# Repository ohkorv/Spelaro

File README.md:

<h1 align="center">

<br> Spelarö <br>

<h4 align="center">
A standalone audio player and optical transmitter powered by the ESP32-S3. Play FLAC and MP3 files from a micro SD card, navigate your library using the 2.8-inch screen and 5-way switch, and output clean digital audio via TOSLINK.
</h4>

<h4 align="center">

<h4 align="center">

# About the project

Spelarö is a custom hardware project that lets you play flac and mp3 files directly from a micro SD card. It sends the data optically via a toslink transmitter with a toslink cable. There was no product like this, so i decided to make my own for me and my dad.

## How It Works

* **Storage:** Music files are stored on a standard micro SD card. The ESP32-S3 reads the files directly from the card. It then sends it via toslink.
* **Interface:** You use a 2.8-inch TFT display to see your library and a 5-way joystick switch to navigate through your libary of songs. 
* **Audio Output:** The ESP32-S3 processes the audio data and sends it out through a toslink transmitter. This results in perfect audio for audiophiles like me and my dad. 
* **Status LED:** An onboard NeoPixel (WS2812B) provides visual feedback for power status and can be programmed to follow the song's rhythm or anything you want.

## Features

* **ESP32-S3-NANO** microcontroller
* **1x 2.8" TFT Display** 
* **1x 5-way tactile joystick switch** 
* **1x 1-way tactile switch** 
* **1x Micro SD Card Reader** 
* **1x Neopixel WS2812B** 
* **1x Optical Toslink Transmitter (OTJ-5)** 

# Schematic

# PCB

# Bill Of Materials

| Designator | Footprint | Qty | Value | Link | Price (USD) |
| :--- | :--- | :---: | :--- | :--- | :---: |
| A1 | `MODULE_NANO-ESP32-ENTRY` | 1 | Arduino_Nano_ESP32 | [Electrokit](https://www.electrokit.com/utvecklingskort-esp32-s3-nano-kompatibelt) | $16.72 |
| C1 | `1206` | 1 | 100nF | [Electrokit](https://www.electrokit.com/kondensator-1206-x7r-100nf-10) | $1.05 |
| J1 | `PinHeader_1x14_P2.54mm_Vertical` | 1 | Conn_01x14_Pin | [Amazon](https://www.amazon.se/gp/product/B09Z29CGY1/ref=ox_sc_act_image_1?smid=A3LA1TDA4Q3SUA&psc=1) | $13.67 |
| LED1 | `WS2812B` | 1 | WS2812B | [Electrokit](https://www.electrokit.com/led-smd5050-rgb-adresserbar-sk6812) | $1.31 |
| R1, R2, R3 | `1206` | 3 | 10k | [Electrokit](https://www.electrokit.com/motstand-10kohm-0.25w-smd-1206) | $1.05 |
| S1 | `SW_VS-1213-67-160GF` | 1 | VS-1213-67-160GF | [Electrokit](https://www.electrokit.com/tryckknapp-pcb-12x12x5mm) | $1.35 |
| SW1 | `C145910` | 1 | K1-1506SN-01 | [Electrokit](https://www.electrokit.com/joystick-navigationsknapp-5-vags-smd-10x10mm-1) | $1.95 |
| TF1 | `TF-SMD_TF-012` | 1 | TF-CARD H1.8 SY | [Electrokit](https://www.electrokit.com/kontakt-microsd) | $1.37 |
| U3 | `toslink` | 1 | OTJ-5 | [Electrokit](https://www.electrokit.com/toslink-optisk-sandare-pcb) | $2.94 |
| PCB | - | 5 | - | [JLCPCB](https://jlcpcb.com/) | $2.10 |
| **Shipping** | - | - | - | - | $33.01 |
| **Total** | - | - | - | - | **$76.52** |

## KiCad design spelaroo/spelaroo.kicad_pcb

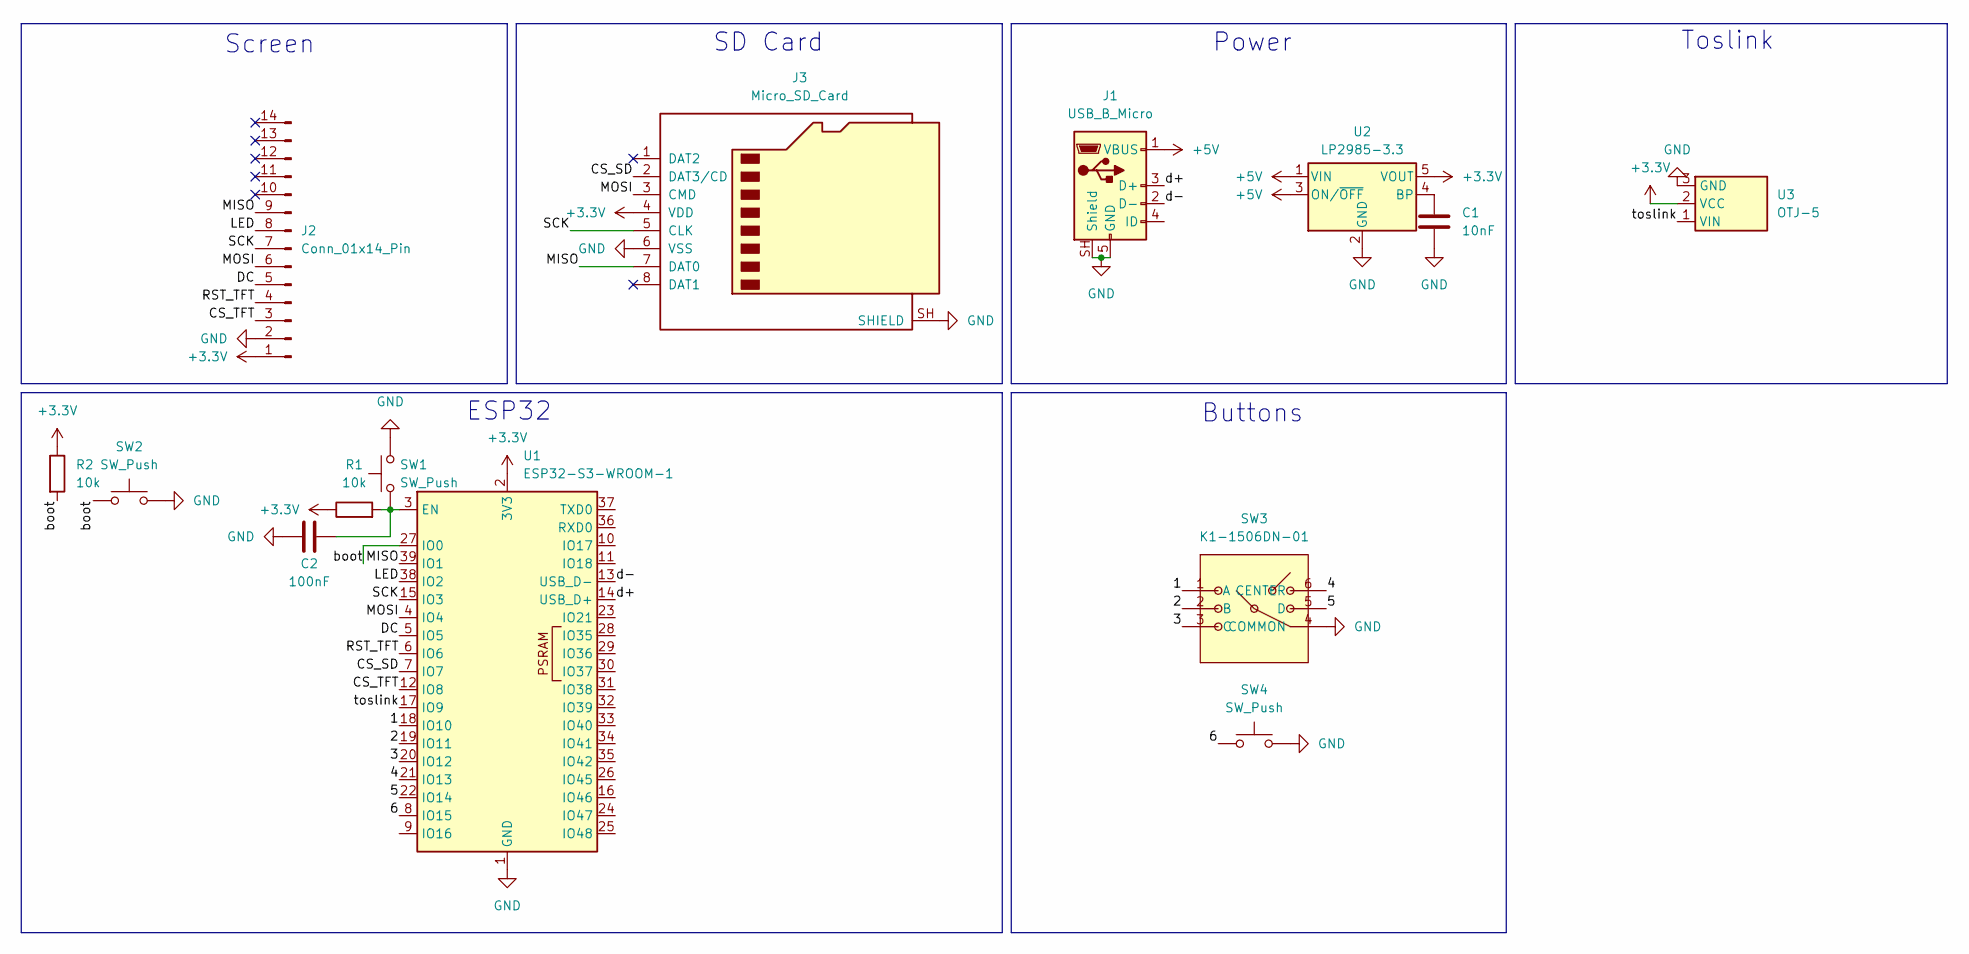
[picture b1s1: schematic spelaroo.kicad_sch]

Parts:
C1: 10nF; C_1206_3216Metric
C2: 100nF; C_1206_3216Metric
J1: USB_B_Micro; USB_Micro-B_Amphenol_10103594-0001LF_Horizontal
J2: Conn_01x14_Pin; PinHeader_1x14_P2.54mm_Vertical
J3: Micro_SD_Card; TF-SMD_TF-012
R1, R2: 10k; R_1206_3216Metric
SW1, SW2: SW_Push; KSR221GLFS_CNK
SW3: K1-1506DN-01; SW-TH_K1-1506DN-01; MPN K1-1506DN-01; LCSC Part C145911
SW4: SW_Push; SW_PUSH-12mm
U1: ESP32-S3-WROOM-1
U2: LP2985-3.3; SOT-23-5
U3: OTJ-5; toslink

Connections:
+3.3V: J2.1, J3.4 (VDD), R1.1, R2.1, U1.2 (3V3), U2.5 (VOUT), U3.2 (VCC)
+5V: J1.1 (VBUS), U2.1 (VIN), U2.3 (ON/~OFF)
/1: SW3.1 (A), U1.18 (IO10)
/2: SW3.2 (B), U1.19 (IO11)
/3: SW3.3 (C), U1.20 (IO12)
/4: SW3.6 (CENTER), U1.21 (IO13)
/5: SW3.5 (D), U1.22 (IO14)
/6: SW4.1, U1.8 (IO15)
/CS_SD: J3.2 (DAT3/CD), U1.7 (IO7)
/CS_TFT: J2.3, U1.12 (IO8)
/DC: J2.5, U1.5 (IO5)
/LED: J2.8, U1.38 (IO2)
/MISO: J2.9, J3.7 (DAT0), U1.39 (IO1)
/MOSI: J2.6, J3.3 (CMD), U1.4 (IO4)
/RST_TFT: J2.4, U1.6 (IO6)
/SCK: J2.7, J3.5 (CLK), U1.15 (IO3)
/boot: R2.2, SW2.1, U1.27 (IO0)
/d+: J1.3 (D+), U1.14 (USB_D+)
/d-: J1.2 (D-), U1.13 (USB_D-)
/toslink: U1.17 (IO9), U3.1 (VIN)
GND: C1.2, C2.2, J1.5 (GND), J1.SH (Shield), J2.2, J3.6 (VSS), J3.SH (SHIELD), SW1.2, SW2.2, SW3.4 (COMMON), SW4.2, U1.1 (GND), U1.40 (GND), U1.41 (GND), U2.2 (GND), U3.3 (GND)
unnamed: C2.1, R1.2, SW1.1, U1.3 (EN)
unnamed: C1.1, U2.4 (BP)

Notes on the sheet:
Screen
Toslink
ESP32
Buttons
SD Card
Power

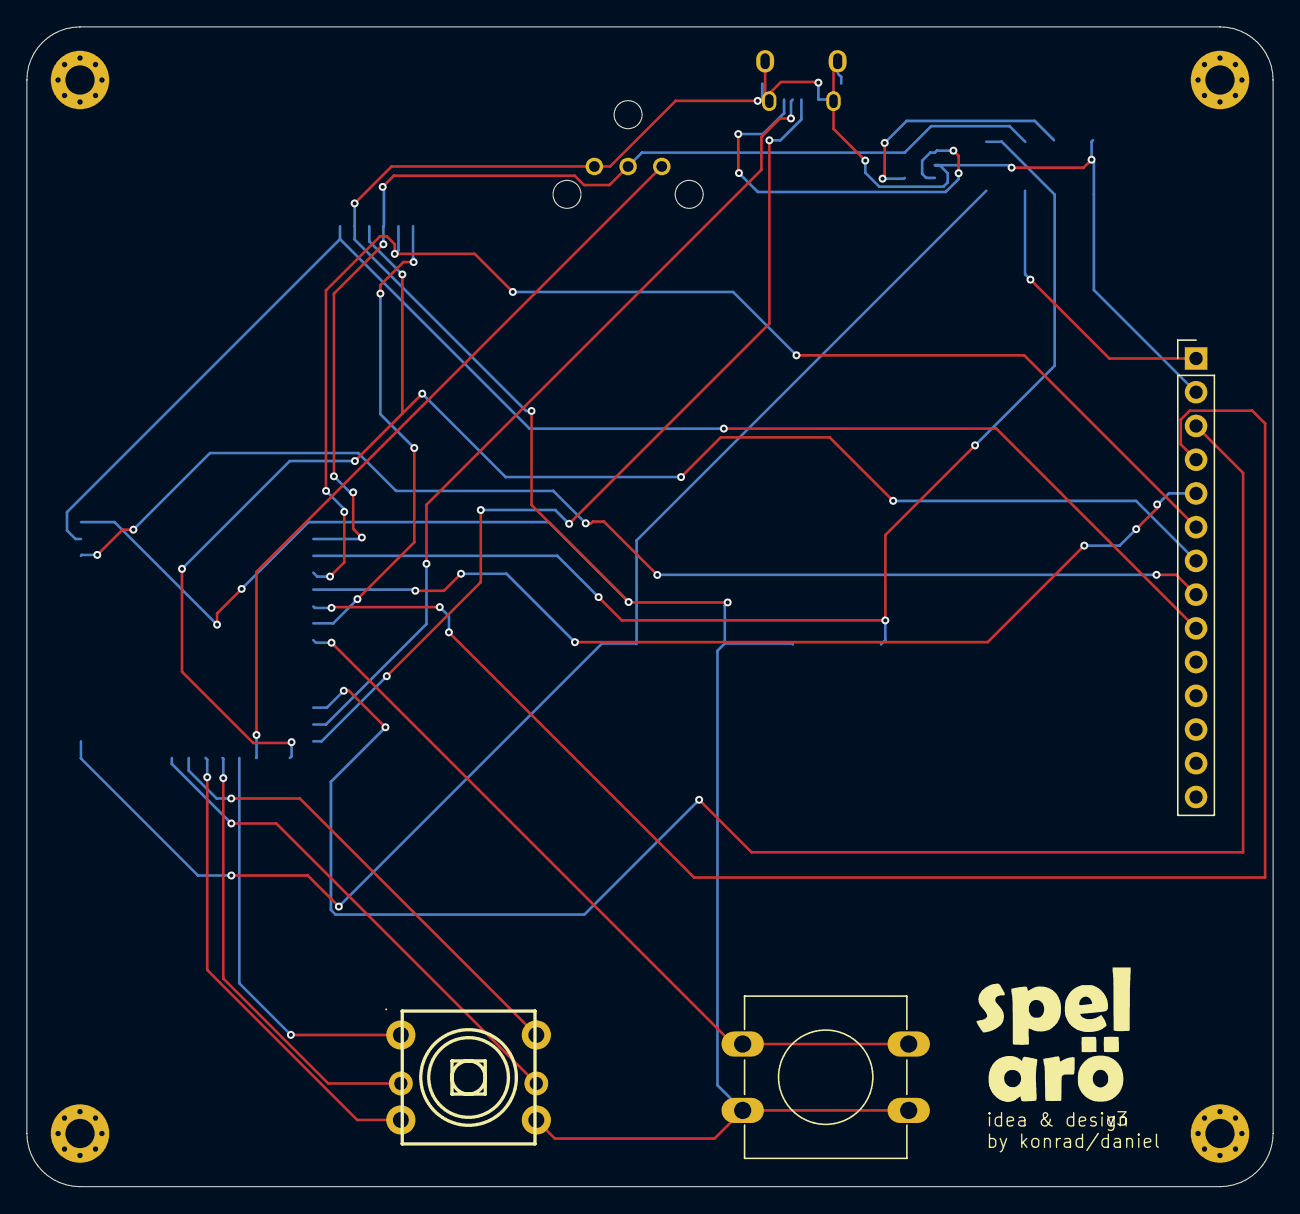
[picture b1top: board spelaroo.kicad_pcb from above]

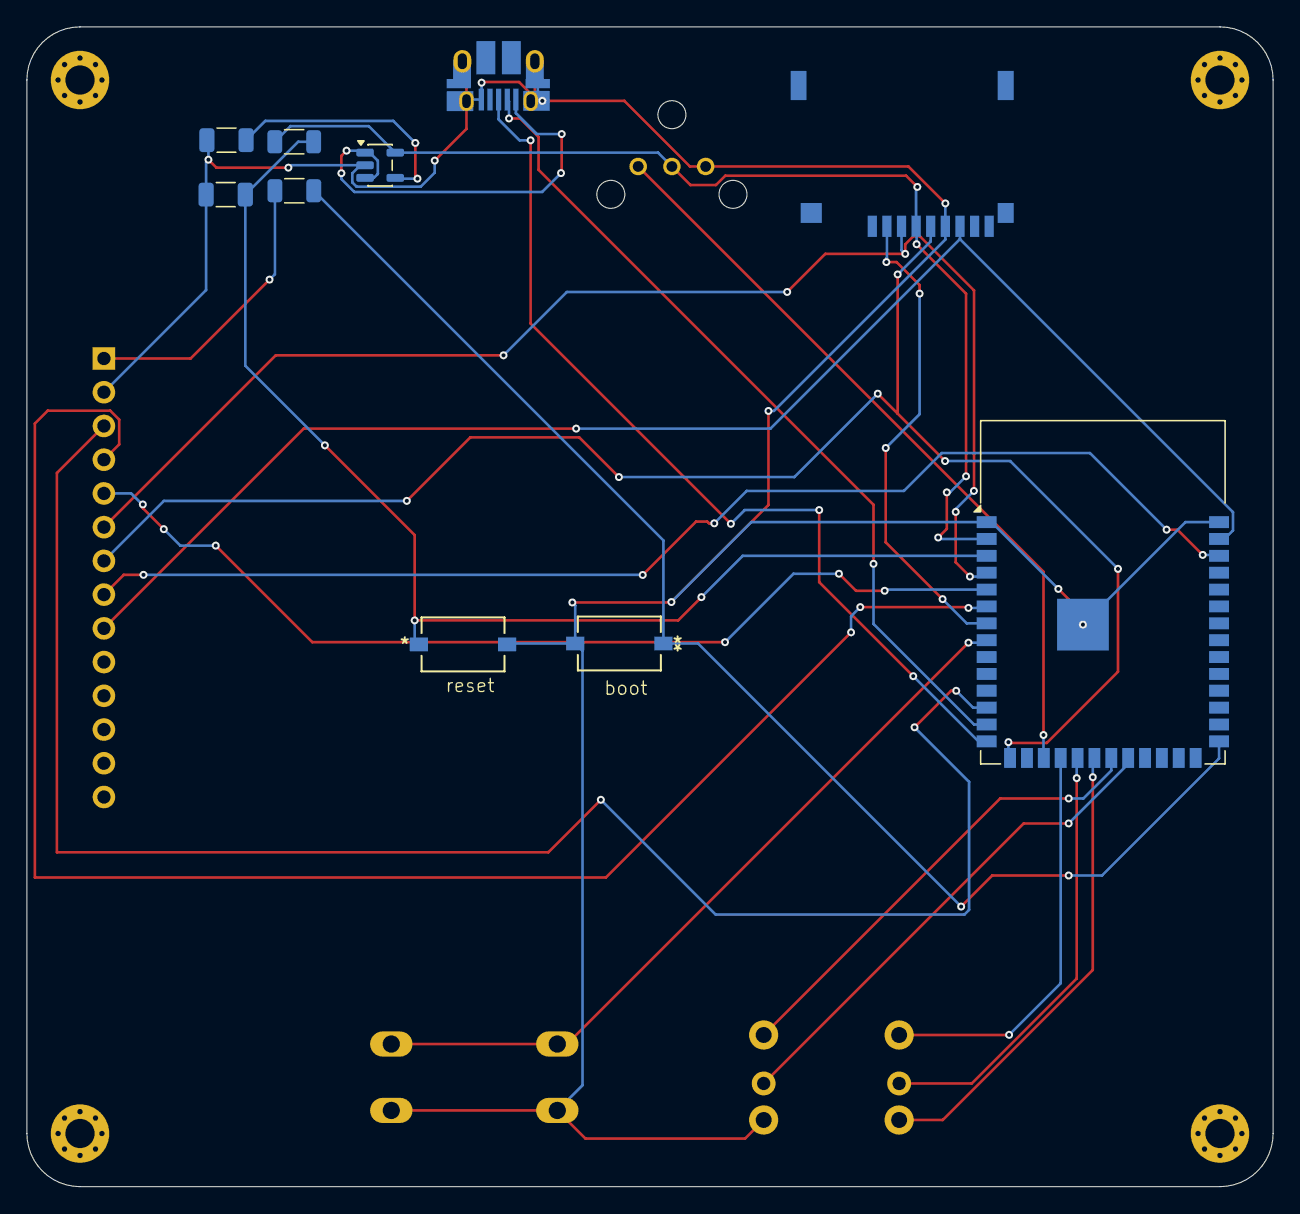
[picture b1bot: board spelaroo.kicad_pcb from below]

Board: 2 copper layers, 93.8 x 87.3 mm, 14 parts (10 on the bottom side), 23 nets.

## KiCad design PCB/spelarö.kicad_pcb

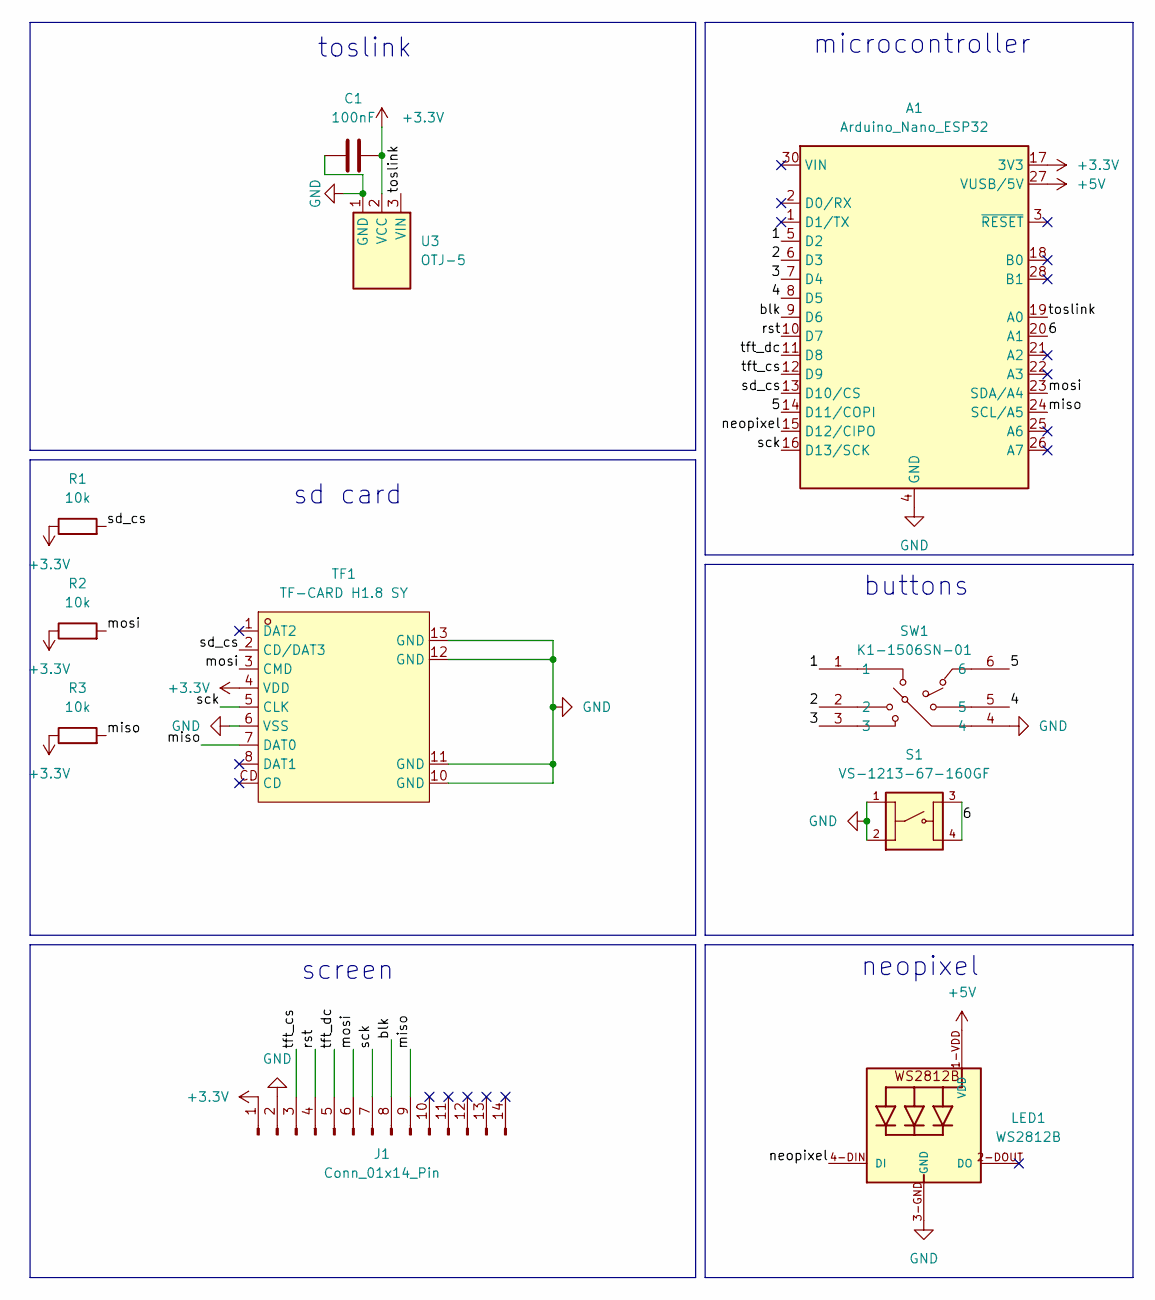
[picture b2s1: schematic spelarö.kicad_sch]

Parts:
A1: Arduino_Nano_ESP32; MODULE_NANO-ESP32-ENTRY
C1: 100nF; C_1206_3216Metric
J1: Conn_01x14_Pin; PinHeader_1x14_P2.54mm_Vertical
LED1: WS2812B
R1, R2, R3: 10k; R_1206_3216Metric
S1: VS-1213-67-160GF; SW_VS-1213-67-160GF; PARTREV N/A
SW1: K1-1506SN-01; C145910; MPN K1-1506SN-01; LCSC Part C145910
TF1: TF-CARD H1.8 SY; TF-SMD_TF-012; MPN TF-CARD H1.8 SY; LCSC Part C7529391
U3: OTJ-5; toslink

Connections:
+3.3V: A1.17 (3V3), C1.1, J1.1, R1.1, R2.1, R3.1, TF1.4 (VDD), U3.2 (VCC)
+5V: A1.27 (VUSB/5V), LED1.1-VDD (VDD)
/1: A1.5 (D2), SW1.1
/2: A1.6 (D3), SW1.2
/3: A1.7 (D4), SW1.3
/4: A1.8 (D5), SW1.5
/5: A1.14 (D11/COPI), SW1.6
/6: A1.20 (A1), S1.3, S1.4
/blk: A1.9 (D6), J1.8
/miso: A1.24 (SCL/A5), J1.9, R3.2, TF1.7 (DAT0)
/mosi: A1.23 (SDA/A4), J1.6, R2.2, TF1.3 (CMD)
/neopixel: A1.15 (D12/CIPO), LED1.4-DIN (DI)
/rst: A1.10 (D7), J1.4
/sck: A1.16 (D13/SCK), J1.7, TF1.5 (CLK)
/sd_cs: A1.13 (D10/CS), R1.2, TF1.2 (CD/DAT3)
/tft_cs: A1.12 (D9), J1.3
/tft_dc: A1.11 (D8), J1.5
/toslink: A1.19 (A0), U3.3 (VIN)
GND: A1.4 (GND), A1.29 (GND), C1.2, J1.2, LED1.3-GND (GND), S1.1, S1.2, SW1.4, TF1.6 (VSS), TF1.10 (GND), TF1.11 (GND), TF1.12 (GND), TF1.13 (GND), U3.1 (GND)

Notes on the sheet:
buttons
sd card
neopixel
toslink
microcontroller
screen

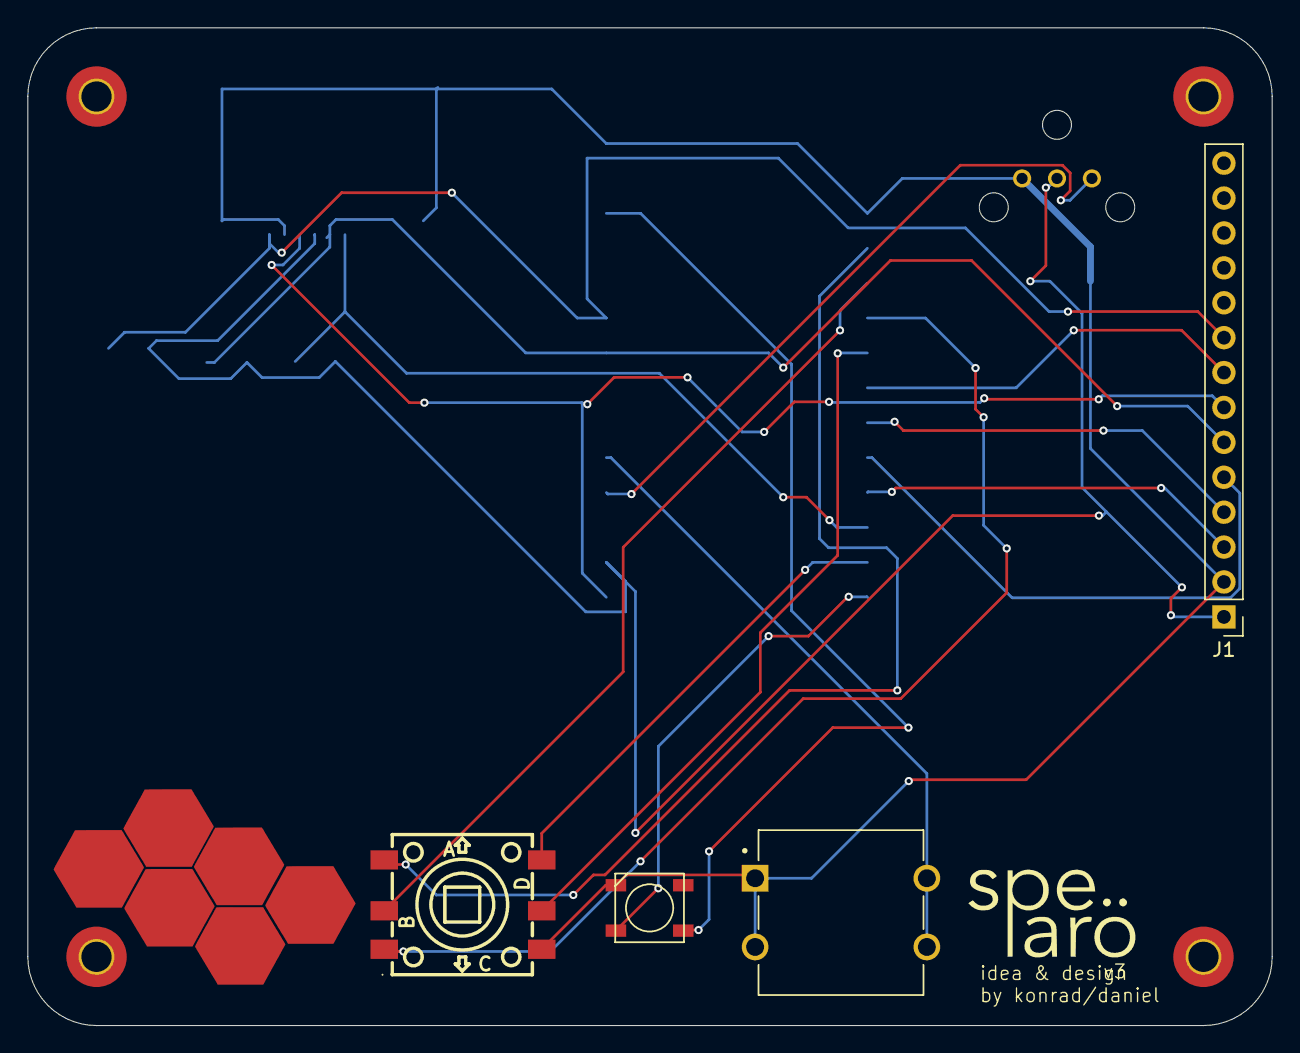
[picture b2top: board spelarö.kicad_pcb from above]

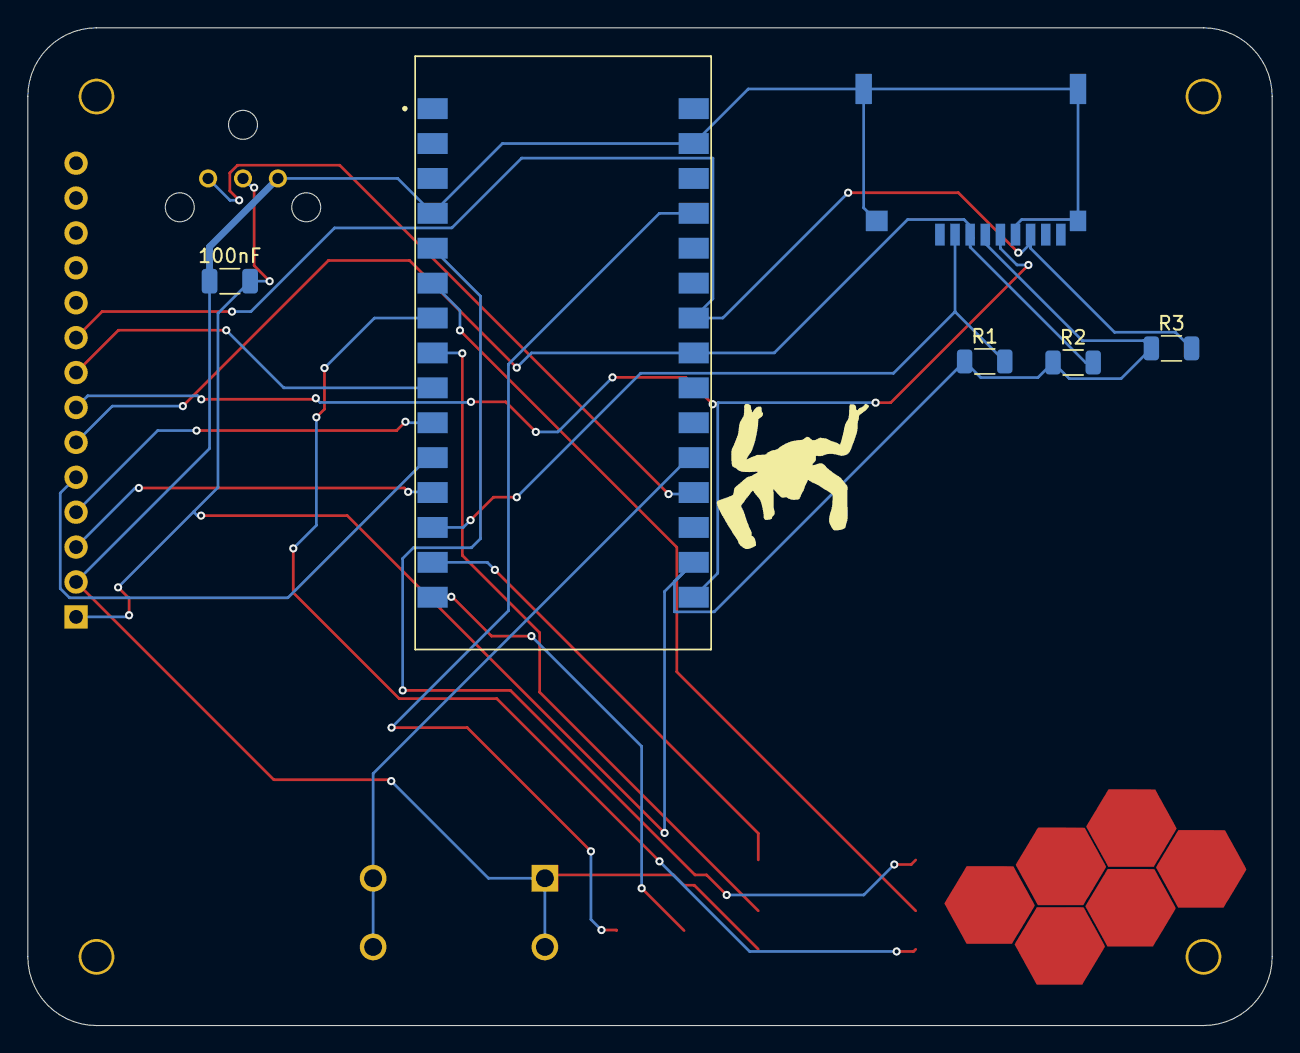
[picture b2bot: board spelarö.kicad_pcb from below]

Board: 2 copper layers, 90.6 x 72.6 mm, 11 parts (7 on the bottom side), 19 nets.

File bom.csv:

Designator,Footprint,,,Quantity,Value,,Link
A1,MODULE_NANO-ESP32-ENTRY,,,1,Arduino_Nano_ESP32,,https://www.electrokit.com/utvecklingskort-esp32-s3-nano-kom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
C1,1206,,,1,100nF,,https://www.electrokit.com/kondensator-1206-x7r-100nf-10
J1,PinHeader_1x14_P2.54mm_Vertical,,,1,Conn_01x14_Pin,,https://www.amazon.se/gp/product/B09Z29CGY1/ref=ox_sc_act_im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
LED1,WS2812B,,,1,WS2812B,,https://www.electrokit.com/led-smd5050-rgb-adresserbar-sk6812
"R1, R2, R3",1206,,,3,10k,,https://www.electrokit.com/motstand-10kohm-0.25w-smd-1206
S1,SW_VS-1213-67-160GF,,,1,VS-1213-67-160GF,,https://www.electrokit.com/tryckknapp-pcb-12x12x5mm
SW1,C145910,,,1,K1-1506SN-01,,https://www.electrokit.com/joystick-navigationsknapp-5-vags-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
TF1,TF-SMD_TF-012,,,1,TF-CARD H1.8 SY,,https://www.electrokit.com/kontakt-microsd
U3,toslink,,,1,OTJ-5,,https://www.electrokit.com/toslink-optisk-sandare-pcb
PCB,-,,,5,PCB,,https://jlcpcb.com/
Shipping,-,,,1,Shipping ($33.01),,
Total,-,,,,-, ,$76.52

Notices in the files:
README.md:
License: MIT
